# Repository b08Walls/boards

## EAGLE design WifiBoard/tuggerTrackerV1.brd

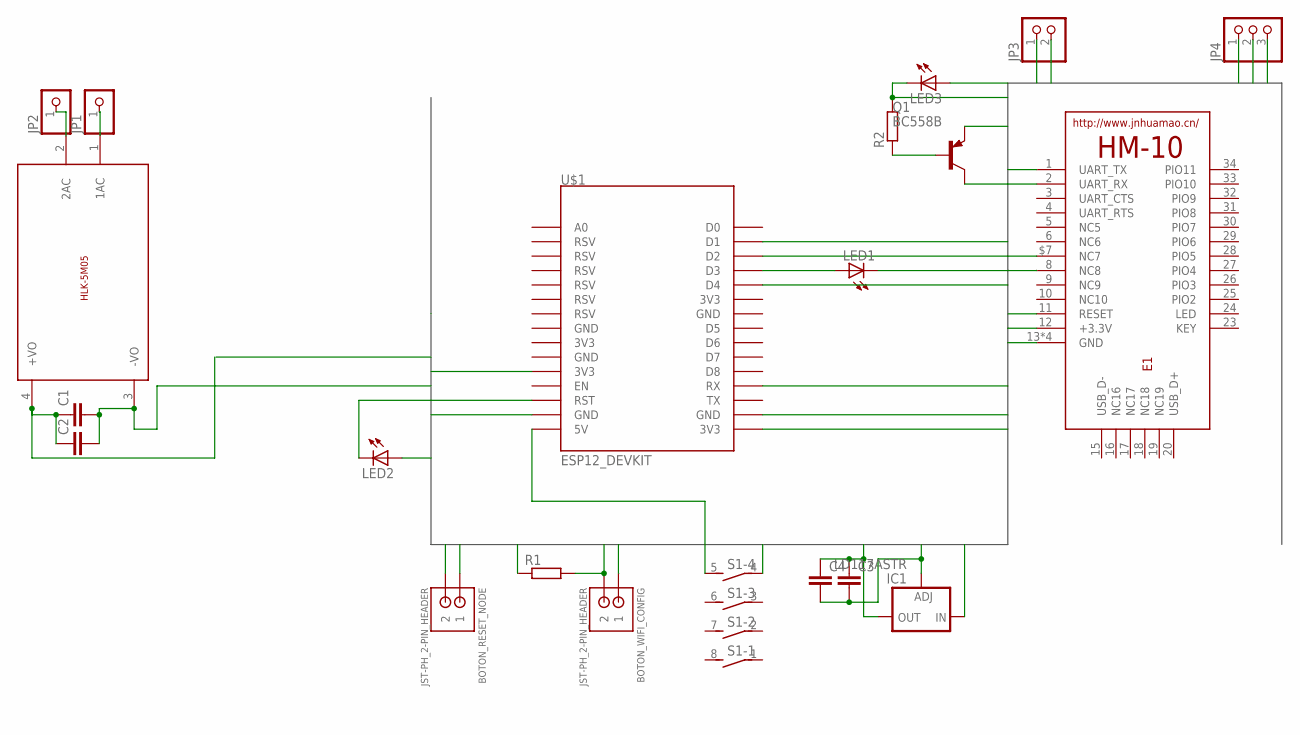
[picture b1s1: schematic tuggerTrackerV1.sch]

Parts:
BOTON_RESET_NODE: JST-PH_2-PIN_HEADER; JST_B2B-PH_HEADER
BOTON_WIFI_CONFIG: JST-PH_2-PIN_HEADER; JST_B2B-PH_HEADER
C1, C2, C3, C4: CC0603; C0603
E1: HM-10-BOARD; 26.9X13X2.2_BOARD
IC1: LD117ASTR; SOT223
JP1, JP2: PINHD-1X1; 1X01
JP3: PINHD-1X2; 1X02
JP4: PINHD-1X3; 1X03
LED1, LED2, LED3: LEDCHIPLED_1206; CHIPLED_1206
Q1: BC558B; TO92-EBC
R1, R2: R0207/10; 0207/10
S1: DIP04S
U$1: ESP12_DEVKIT
U$2: 5VDC/5W; HLK-5M05

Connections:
BTPG1: E1.$7 (NC7), JP4.1
BTPG2: E1.8 (NC8), JP4.2
BTRST: E1.11 (RESET), JP4.3
BTVCC: E1.12 (+3.3V), Q1.C
D1: LED3.C, R2.2, U$1.D1
D2: BOTON_WIFI_CONFIG.P2 (2), R1.2, U$1.D2
GND: BOTON_RESET_NODE.P2 (2), C1.2, C2.2, C3.2, C4.2, E1.13 (GND), E1.14 (GND), E1.21 (GND), E1.22 (GND), IC1.1 (ADJ), JP3.1, LED1.C, LED2.C, R1.1, U$1.GND@1 (GND), U$1.GND@3 (GND), U$2.3 (-VO)
unnamed: S1.5 (2), U$1.5V
unnamed: Q1.B, R2.1
unnamed: JP1.1, U$2.1 (1AC)
unnamed: JP2.1, U$2.2 (2AC)
unnamed: LED1.A, U$1.D3
NODRST: BOTON_RESET_NODE.P1 (1), U$1.RST
NRXBTX: E1.1 (UART_TX), U$1.RX
NTXBRX: E1.2 (UART_RX), U$1.D4
V3NODE: BOTON_WIFI_CONFIG.P1 (1), LED2.A, LED3.A, U$1.3V3@0 (3V3), U$1.3V3@2 (3V3)
V3REG: C3.1, C4.1, IC1.4 (OUT), Q1.E
VIN: C1.1, C2.1, IC1.3 (IN), JP3.2, S1.4 (1), U$2.4 (+VO)

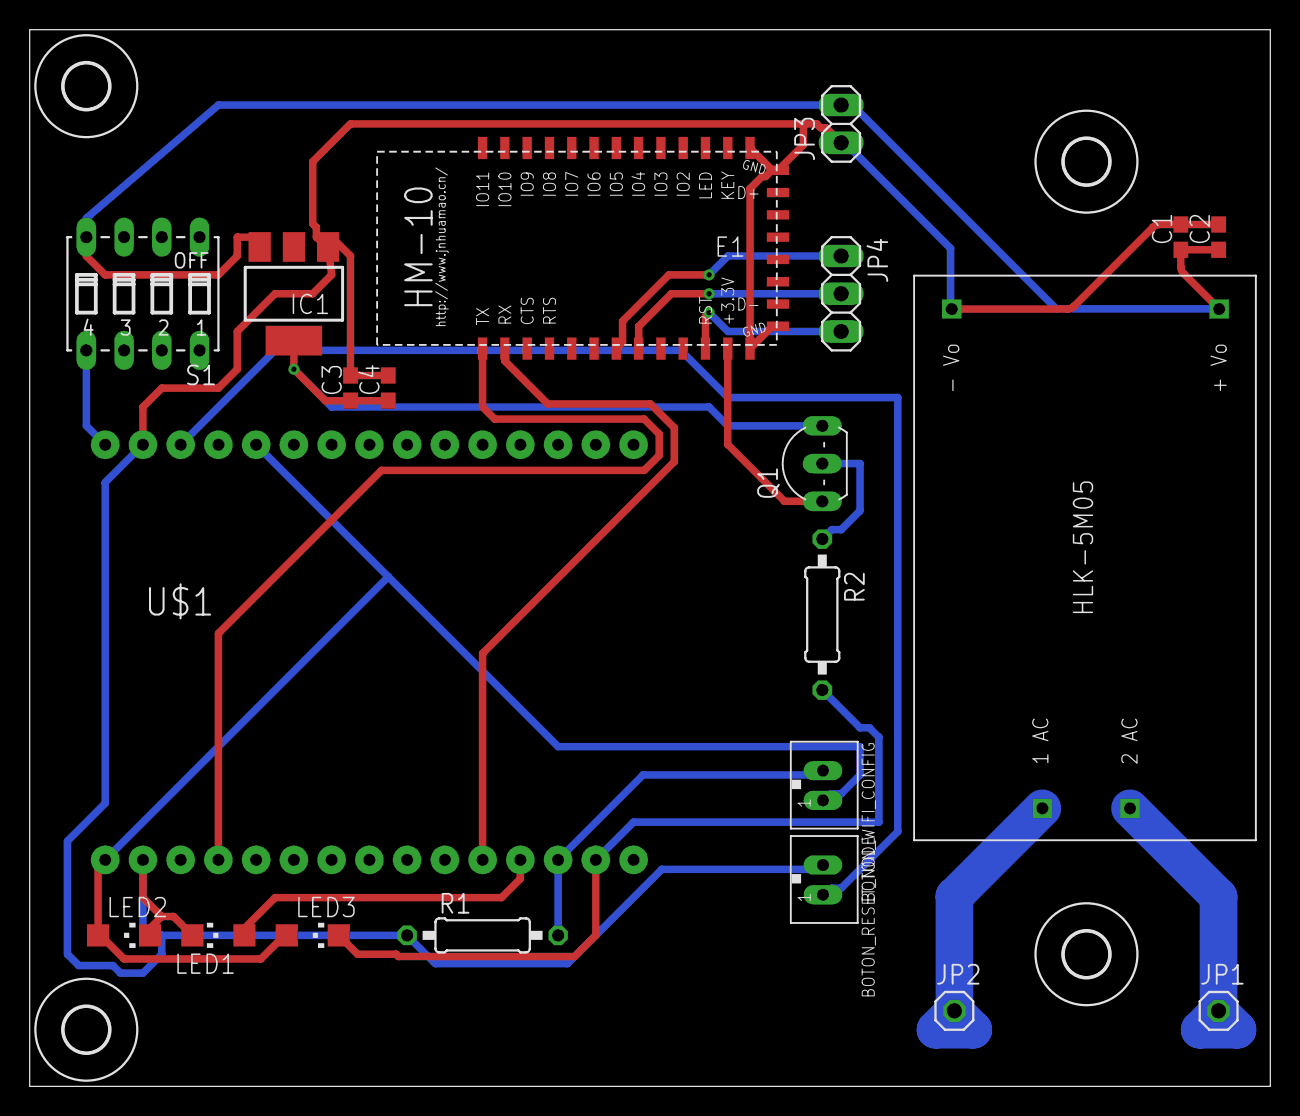
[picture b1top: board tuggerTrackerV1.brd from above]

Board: 2 copper layers, 83.5 x 71.1 mm, 25 parts (0 on the bottom side), 18 nets.

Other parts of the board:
U$6, U$7, U$8, U$9: 3,0
